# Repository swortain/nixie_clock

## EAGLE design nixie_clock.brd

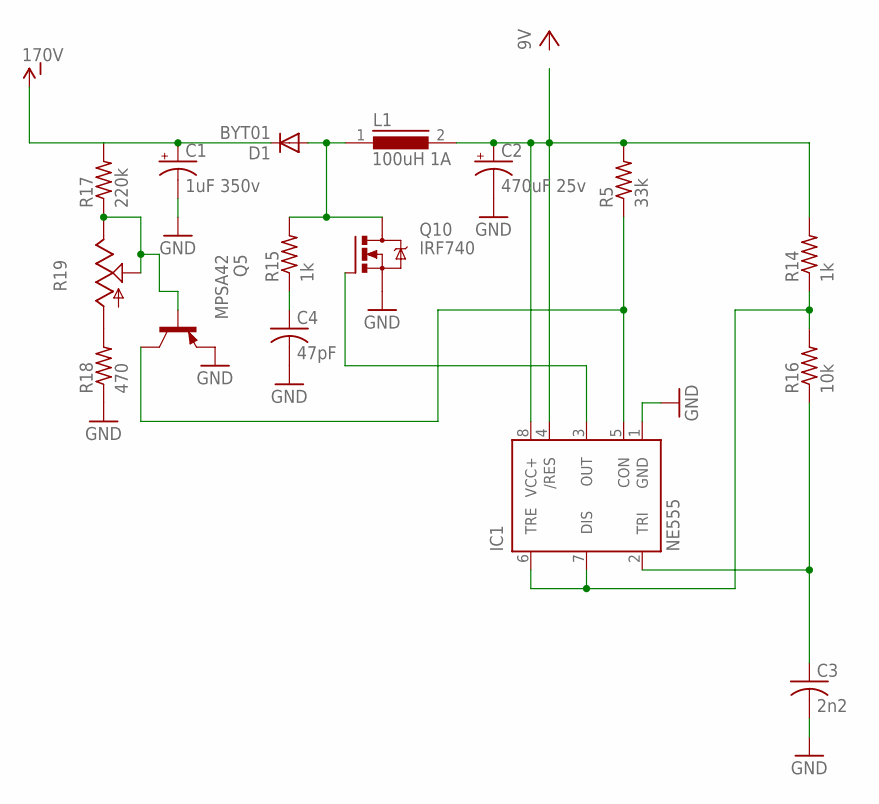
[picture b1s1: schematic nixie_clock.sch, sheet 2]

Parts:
C1: 1uF 350v; E2,5-7
C2: 470uF 25v; E5-10,5
C3: 2n2; C050-024X044
C4: 47pF; C075-032X103
D1: BYT01; F126-10
IC1: NE555; DIL-08
L1: 100uH 1A; MESC26
Q5: MPSA42; TO92-CBE
Q10: IRF740; TO220BV
R5: 33k; 0207/2V
R14, R15: 1k; 0207/2V
R16: 10k; 0207/2V
R17: 220k; 0207/2V
R18: 470; 0207/2V
R19: TRIM_US-B25P; B25P

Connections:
GND: C1.-, C2.-, C3.2, C4.2, IC1.1 (GND), Q5.E, Q10.S, R18.1
unnamed: C2.+, IC1.4 (/RES), IC1.8 (VCC+), L1.2, R5.2, R14.2
unnamed: C4.1, R15.1
unnamed: D1.A, L1.1, Q10.D, R15.2
unnamed: Q5.B, R17.1, R19.E, R19.S
unnamed: R18.2, R19.A
unnamed: IC1.6 (TRE), IC1.7 (DIS), R14.1, R16.2
unnamed: IC1.3 (OUT), Q10.G
unnamed: IC1.5 (CON), Q5.C, R5.1
unnamed: C3.1, IC1.2 (TRI), R16.1
VCC-ISO: C1.+, D1.C, R17.2

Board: 2 copper layers, 16 parts (0 on the bottom side), 11 nets, no tracks yet.

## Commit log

2016-01-16 init project

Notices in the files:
parts and their libraries:
SparkFun-Aesthetics: Licensing: Creative Commons ShareAlike 4.0 International - https://creativecommons.org/licenses/by-sa/4.0
